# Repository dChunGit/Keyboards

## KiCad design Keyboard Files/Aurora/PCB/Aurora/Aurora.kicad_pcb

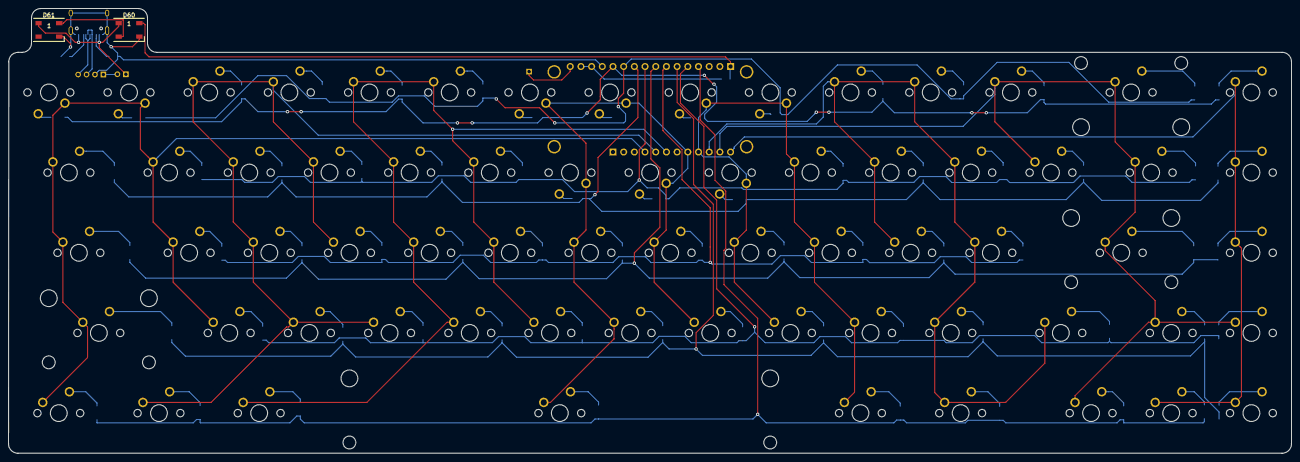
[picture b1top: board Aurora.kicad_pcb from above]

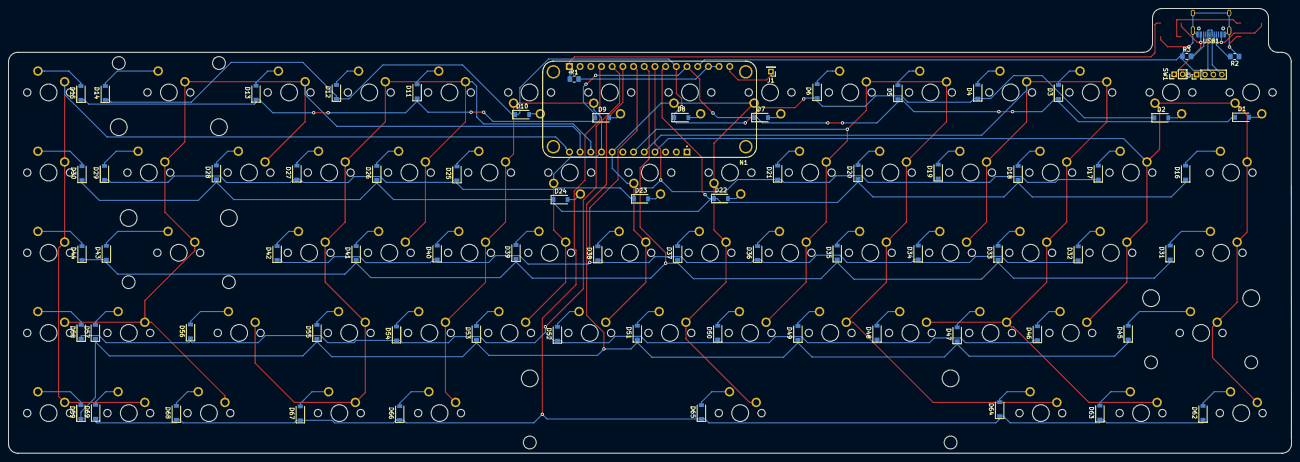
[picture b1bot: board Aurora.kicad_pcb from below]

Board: 2 copper layers, 304.9 x 105.7 mm, 144 parts (75 on the bottom side), 95 nets.

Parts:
D1, D2, D3, D4, D5, D6, D7, D8, D9, D10, D11, D12, D13, D14, D15, D16, D17, D18, D19, D20, D21, D22, D23, D24, D25, D26, D27, D28, D29, D30, D31, D32, D33, D34, D35, D36, D37, D38, D39, D40, D41, D42, D43, D44, D45, D46, D47, D48, D49, D50, D51, D52, D53, D54, D55, D56, D57, D58, D59, D62, D63, D64, D65, D66, D67, D68, D69: D_Small; D_SOD-123
D60, D61: WS2812B; LED_WS2812B_PLCC4_5.0x5.0mm_P3.2mm
J1: Conn_01x01; PinHeader_1x01_P2.00mm_Vertical
J2: Conn_01x04; PinHeader_1x04_P2.00mm_Vertical
MX1, MX2, MX3, MX4, MX5, MX6, MX7, MX8, MX9, MX10, MX11, MX12, MX13, MX15, MX17, MX18, MX19, MX20, MX21, MX22, MX23, MX24, MX25, MX26, MX27, MX28, MX30, MX32, MX33, MX34, MX35, MX36, MX37, MX38, MX39, MX40, MX41, MX42, MX44, MX46, MX47, MX48, MX49, MX50, MX51, MX52, MX53, MX54, MX55, MX57, MX58, MX59, MX66, MX67: MX-NoLED; MXOnly-1U-NoLED
MX14: MX-NoLED; MXOnly-2U-NoLED
MX16, MX29: MX-NoLED; MXOnly-1.5U-NoLED
MX31, MX56: MX-NoLED; MXOnly-1.75U-NoLED
MX43, MX45: MX-NoLED; MXOnly-2.25U-ReversedStabilizers-NoLED
MX60, MX61, MX62, MX64, MX65: MX-NoLED; MXOnly-1.25U-NoLED
MX63: MX-NoLED; MXOnly-6.25U-ReversedStabilizers-NoLED
N1: nrf52; adafruit_feather
R1, R2, R3: R_Small; R_0805_2012Metric_Pad1.15x1.40mm_HandSolder
SW1: SW_SPST; PinHeader_1x02_P2.00mm_Vertical
USB1: HRO-TYPE-C-31-M-12

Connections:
+3V3: N1.2, N1.3, R1.2
+5V: D60.1, D61.1, SW1.1, USB1.2, USB1.11
Col0: MX1.1, MX2.1, MX16.1, MX17.1, MX31.1, MX32.1, MX45.1, MX46.1, MX60.1, N1.20
Col1: MX3.1, MX4.1, MX18.1, MX19.1, MX33.1, MX34.1, MX47.1, MX48.1, MX61.1, N1.21
Col2: MX5.1, MX6.1, MX20.1, MX21.1, MX35.1, MX36.1, MX49.1, MX50.1, MX62.1, N1.22
Col3: MX7.1, MX8.1, MX22.1, MX23.1, MX37.1, MX38.1, MX51.1, MX52.1, MX63.1, N1.24
Col4: MX9.1, MX10.1, MX24.1, MX25.1, MX39.1, MX40.1, MX53.1, MX54.1, MX64.1, N1.25
Col5: MX11.1, MX12.1, MX26.1, MX27.1, MX41.1, MX42.1, MX55.1, MX56.1, MX65.1, N1.26
Col6: MX13.1, MX14.1, MX28.1, MX29.1, MX43.1, MX57.1, MX58.1, MX66.1, N1.27
Col7: MX15.1, MX30.1, MX44.1, MX59.1, MX67.1, N1.28
D+: J2.3, USB1.6, USB1.8
D-: J2.4, USB1.5, USB1.7
GND: D60.3, D61.3, J2.2, N1.4, R2.1, R3.1, USB1.1, USB1.12, USB1.13
LED: D60.4, N1.16, R1.1
unnamed: D1.2, MX1.2
unnamed: D2.2, MX2.2
unnamed: D3.2, MX3.2
unnamed: D4.2, MX4.2
unnamed: D5.2, MX5.2
unnamed: D6.2, MX6.2
unnamed: D7.2, MX7.2
unnamed: D8.2, MX8.2
unnamed: D9.2, MX9.2
unnamed: D10.2, MX10.2
unnamed: D11.2, MX11.2
unnamed: D12.2, MX12.2
unnamed: D13.2, MX13.2
unnamed: D14.2, MX14.2
unnamed: D15.2, MX15.2
unnamed: D16.2, MX16.2
unnamed: D17.2, MX17.2
unnamed: D18.2, MX18.2
unnamed: D19.2, MX19.2
unnamed: D20.2, MX20.2
unnamed: D21.2, MX21.2
unnamed: D22.2, MX22.2
unnamed: D23.2, MX23.2
unnamed: D24.2, MX24.2
unnamed: D25.2, MX25.2
unnamed: D26.2, MX26.2
unnamed: D27.2, MX27.2
unnamed: D28.2, MX28.2
unnamed: D29.2, MX29.2
unnamed: D30.2, MX30.2
unnamed: D31.2, MX31.2
unnamed: D32.2, MX32.2
unnamed: D33.2, MX33.2
unnamed: D34.2, MX34.2
unnamed: D35.2, MX35.2
unnamed: D36.2, MX36.2
unnamed: D37.2, MX37.2
unnamed: D38.2, MX38.2
unnamed: D39.2, MX39.2
unnamed: D40.2, MX40.2
unnamed: D41.2, MX41.2
unnamed: D42.2, MX42.2
unnamed: D43.2, MX43.2
unnamed: D44.2, MX44.2
unnamed: D45.2, MX45.2
unnamed: D46.2, MX46.2
unnamed: D47.2, MX47.2
unnamed: D48.2, MX48.2
unnamed: D49.2, MX49.2
unnamed: D50.2, MX50.2
unnamed: D51.2, MX51.2
unnamed: D52.2, MX52.2
unnamed: D53.2, MX53.2
unnamed: D54.2, MX54.2
unnamed: D55.2, MX55.2
unnamed: D56.2, MX56.2
unnamed: D57.2, MX57.2
unnamed: D58.2, MX58.2
unnamed: D59.2, MX59.2
unnamed: D60.2, D61.4
unnamed: D62.2, MX60.2
unnamed: D63.2, MX61.2
unnamed: D64.2, MX62.2
unnamed: D65.2, MX63.2
unnamed: D66.2, MX64.2
unnamed: D67.2, MX65.2
unnamed: D68.2, MX66.2
unnamed: D69.2, MX67.2
unnamed: J1.1, N1.1
unnamed: J2.1, SW1.2
unnamed: R2.2, USB1.4
unnamed: R3.2, USB1.10
Row0: D1.1, D3.1, D5.1, D7.1, D9.1, D11.1, D13.1, D15.1, N1.5
Row1: D2.1, D4.1, D6.1, D8.1, D10.1, D12.1, D14.1, N1.6
Row2: D16.1, D18.1, D20.1, D22.1, D24.1, D26.1, D28.1, D30.1, N1.7
Row3: D17.1, D19.1, D21.1, D23.1, D25.1, D27.1, D29.1, N1.8
Row4: D31.1, D33.1, D35.1, D37.1, D39.1, D41.1, D43.1, D44.1, N1.9
Row5: D32.1, D34.1, D36.1, D38.1, D40.1, D42.1, N1.10
Row6: D45.1, D47.1, D49.1, D51.1, D53.1, D55.1, D57.1, D59.1, N1.11
Row7: D46.1, D48.1, D50.1, D52.1, D54.1, D56.1, D58.1, N1.12
Row8: D62.1, D63.1, D64.1, D65.1, D66.1, D67.1, D68.1, D69.1, N1.13

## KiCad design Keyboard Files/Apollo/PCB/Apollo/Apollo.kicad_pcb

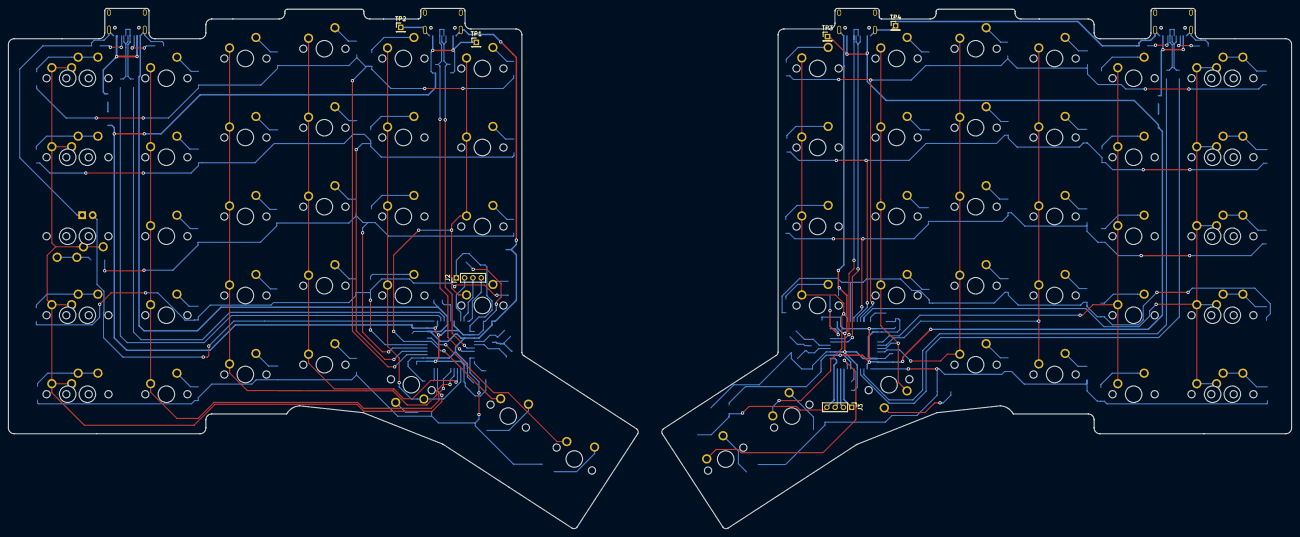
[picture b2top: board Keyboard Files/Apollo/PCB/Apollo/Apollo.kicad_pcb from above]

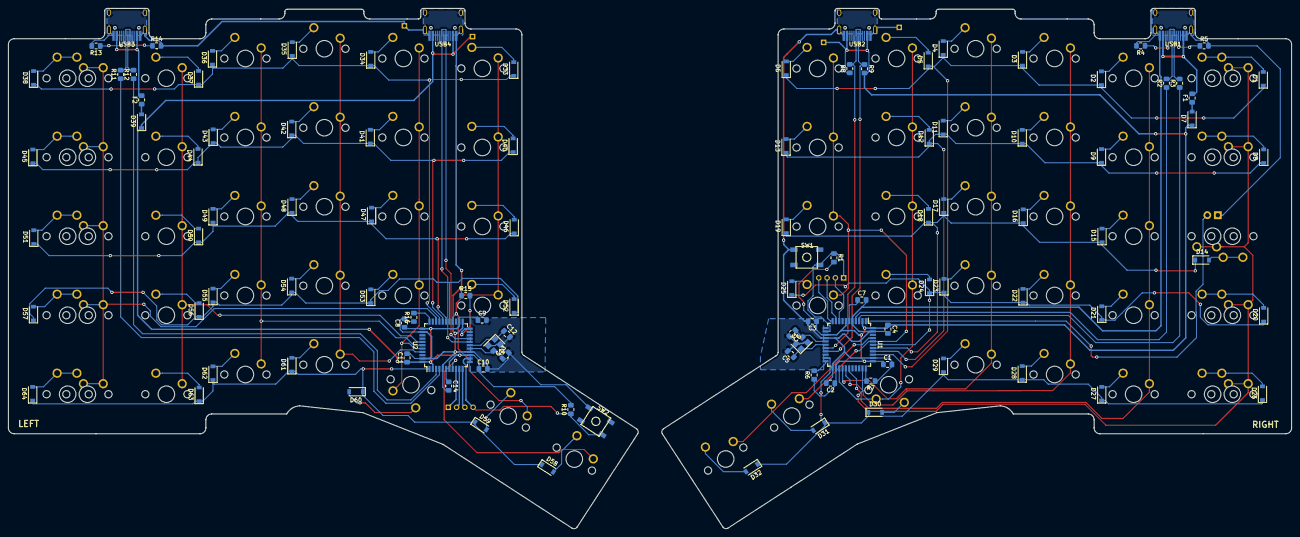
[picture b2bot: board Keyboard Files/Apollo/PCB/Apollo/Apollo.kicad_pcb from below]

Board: 2 copper layers, 309.4 x 125.5 mm, 184 parts (106 on the bottom side), 129 nets.

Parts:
C1, C2, C3, C8, C9, C10: 0.1uF; C_0805_2012Metric_Pad1.15x1.40mm_HandSolder
C4, C11: 10uF; C_0805_2012Metric_Pad1.15x1.40mm_HandSolder
C5, C6, C12, C13: 22pF; C_0805_2012Metric_Pad1.15x1.40mm_HandSolder
C7, C14: 1uF; C_0805_2012Metric_Pad1.15x1.40mm_HandSolder
D1, D2, D3, D4, D5, D6, D8, D9, D10, D11, D12, D13, D14, D15, D16, D17, D18, D19, D20, D21, D22, D23, D24, D25, D26, D27, D28, D29, D30, D31, D32, D33, D34, D35, D36, D37, D38, D40, D41, D42, D43, D44, D45, D46, D47, D48, D49, D50, D51, D52, D53, D54, D55, D56, D57, D58, D59, D60, D61, D62, D63, D64: D_Small; D_SOD-123
D7, D39: Schottky; D_SOD-123
F1, F2: Polyfuse_Small; Fuse_0805_2012Metric_Pad1.15x1.40mm_HandSolder
J2, J3: Conn_01x04; PinHeader_1x04_P2.00mm_Vertical
MX1, MX7, MX13, MX19, MX25, MX37, MX43, MX49, MX55, MX62: MX-NoLED; MXOnly-1.5U-NoLED
MX2, MX3, MX4, MX5, MX6, MX8, MX9, MX10, MX11, MX12, MX14, MX15, MX16, MX17, MX18, MX20, MX21, MX22, MX23, MX24, MX26, MX27, MX28, MX29, MX32, MX33, MX34, MX35, MX36, MX38, MX39, MX40, MX41, MX42, MX44, MX45, MX46, MX47, MX48, MX50, MX51, MX52, MX53, MX54, MX58, MX59, MX60, MX61, MX63, MX64, MX66, MX67, MX68, MX69, MX70, MX71, MX72: MX-NoLED; MXOnly-1U-NoLED
MX30, MX31, MX56, MX57: MX-NoLED; MXOnly-1.5U-Vertical-NoLED
MX65: MX-LED; MXOnly-1U
R1, R6, R7, R10, R15, R16: 10k; R_0805_2012Metric_Pad1.15x1.40mm_HandSolder
R2, R3, R11, R12: 22; R_0805_2012Metric_Pad1.15x1.40mm_HandSolder
R4, R5, R13, R14: 5.1k; R_0805_2012Metric_Pad1.15x1.40mm_HandSolder
R8, R9: 4.7k; R_0805_2012Metric_Pad1.15x1.40mm_HandSolder
SW1, SW2: SW_Push; SKQGADE010
TP1, TP2, TP3, TP4: TestPoint; PinHeader_1x01_P2.00mm_Vertical
U1, U2: ATmega32U4-MU; TQFP-44_10x10mm_P0.8mm
USB1, USB2, USB3, USB4: HRO-TYPE-C-31-M-12; HRO-TYPE-C-31-M-12-HandSoldering
Y1, Y2: Crystal_GND24_Small; Crystal_SMD_3225-4Pin_3.2x2.5mm

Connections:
+5V: C1.1, C2.1, C3.1, C4.1, D7.1, R1.2, R6.1, R8.1, R9.2, TP1.1, U1.2, U1.7, U1.14, U1.24, U1.34, U1.44, USB2.2, USB2.11
+5VA: C8.1, C9.1, C10.1, C11.1, D39.1, R10.2, TP3.1, U2.2, U2.7, U2.14, U2.24, U2.34, U2.44, USB4.2, USB4.11
CapsLED: MX65.3, U1.1
Col0: MX1.1, MX7.1, MX13.1, MX19.1, MX25.1, MX63.1, MX64.1, MX65.1, MX66.1, MX67.1, U1.32
Col0_1: MX56.1, U2.8
Col1: MX2.1, MX8.1, MX14.1, MX20.1, MX26.1, U1.28
Col1_1: MX32.1, MX38.1, MX44.1, MX50.1, MX57.1, U2.26
Col2: MX3.1, MX9.1, MX15.1, MX21.1, MX27.1, U1.27
Col2_1: MX33.1, MX39.1, MX45.1, MX51.1, MX58.1, U2.40
Col3: MX4.1, MX10.1, MX16.1, MX22.1, MX28.1, U1.26
Col3_1: MX34.1, MX40.1, MX46.1, MX52.1, MX59.1, U2.41
Col4: MX5.1, MX11.1, MX17.1, MX23.1, MX29.1, U1.25
Col4_1: MX35.1, MX41.1, MX47.1, MX53.1, MX60.1, U2.39
Col5: MX6.1, MX12.1, MX18.1, MX24.1, MX30.1, U1.40
Col5_1: MX36.1, MX42.1, MX48.1, MX54.1, MX61.1, U2.38
Col6: MX31.1, U1.41
Col6_1: MX37.1, MX43.1, MX49.1, MX55.1, MX62.1, MX68.1, MX69.1, MX70.1, MX71.1, MX72.1, U2.31
D1_+: R11.1, U2.4
D1_-: R12.1, U2.3
D+: R2.1, U1.4
D-: R3.1, U1.3
GND: C1.2, C2.2, C3.2, C4.2, C5.2, C6.2, C7.2, MX65.4, R4.2, R5.2, R7.1, SW1.1, TP2.1, U1.5, U1.15, U1.23, U1.35, U1.43, USB1.1, USB1.12, USB1.13, USB2.1, USB2.12, USB2.13, Y1.2, Y1.4
GNDA: C8.2, C9.2, C10.2, C11.2, C12.2, C13.2, C14.2, R13.2, R14.2, R15.1, R16.1, SW2.1, TP4.1, U2.5, U2.15, U2.23, U2.35, U2.43, USB3.1, USB3.12, USB3.13, USB4.1, USB4.12, USB4.13, Y2.2, Y2.4
MISO: J2.4, U1.11
MISO_1: J3.3, U2.11
MOSI: J2.3, U1.10
MOSI_1: J3.2, U2.10
unnamed: C5.1, U1.17, Y1.1
unnamed: C6.1, U1.16, Y1.3
unnamed: C7.1, U1.6
unnamed: C12.1, U2.17, Y2.1
unnamed: C13.1, U2.16, Y2.3
unnamed: C14.1, U2.6
unnamed: D1.2, MX1.2, MX63.2
unnamed: D2.2, MX2.2
unnamed: D3.2, MX3.2
unnamed: D4.2, MX4.2
unnamed: D5.2, MX5.2
unnamed: D6.2, MX6.2
unnamed: D7.2, F1.1
unnamed: D8.2, MX7.2, MX64.2
unnamed: D9.2, MX8.2
unnamed: D10.2, MX9.2
unnamed: D11.2, MX10.2
unnamed: D12.2, MX11.2
unnamed: D13.2, MX12.2
unnamed: D14.2, MX13.2, MX65.2
unnamed: D15.2, MX14.2
unnamed: D16.2, MX15.2
unnamed: D17.2, MX16.2
unnamed: D18.2, MX17.2
unnamed: D19.2, MX18.2
unnamed: D20.2, MX19.2, MX66.2
unnamed: D21.2, MX20.2
unnamed: D22.2, MX21.2
unnamed: D23.2, MX22.2
unnamed: D24.2, MX23.2
unnamed: D25.2, MX24.2
unnamed: D26.2, MX25.2, MX67.2
unnamed: D27.2, MX26.2
unnamed: D28.2, MX27.2
unnamed: D29.2, MX28.2
unnamed: D30.2, MX29.2
unnamed: D31.2, MX30.2
unnamed: D32.2, MX31.2
unnamed: D33.2, MX32.2
unnamed: D34.2, MX33.2
unnamed: D35.2, MX34.2
unnamed: D36.2, MX35.2
unnamed: D37.2, MX36.2
unnamed: D38.2, MX37.2, MX68.2
unnamed: D39.2, F2.1
unnamed: D40.2, MX38.2
unnamed: D41.2, MX39.2
unnamed: D42.2, MX40.2
unnamed: D43.2, MX41.2
unnamed: D44.2, MX42.2
unnamed: D45.2, MX43.2, MX69.2
unnamed: D46.2, MX44.2
unnamed: D47.2, MX45.2
unnamed: D48.2, MX46.2
unnamed: D49.2, MX47.2
unnamed: D50.2, MX48.2
unnamed: D51.2, MX49.2, MX70.2
unnamed: D52.2, MX50.2
unnamed: D53.2, MX51.2
unnamed: D54.2, MX52.2
unnamed: D55.2, MX53.2
unnamed: D56.2, MX54.2
unnamed: D57.2, MX55.2, MX71.2
unnamed: D58.2, MX56.2
unnamed: D59.2, MX57.2
unnamed: D60.2, MX58.2
unnamed: D61.2, MX59.2
unnamed: D62.2, MX60.2
unnamed: D63.2, MX61.2
unnamed: D64.2, MX62.2, MX72.2
unnamed: F1.2, USB1.2, USB1.11
unnamed: F2.2, USB3.2, USB3.11
unnamed: R2.2, USB1.6, USB1.8
unnamed: R3.2, USB1.5, USB1.7
unnamed: R4.1, USB1.10
unnamed: R5.1, USB1.4
unnamed: R6.2, U1.22
unnamed: R7.2, U1.33
unnamed: R11.2, USB3.6, USB3.8
unnamed: R12.2, USB3.5, USB3.7
unnamed: R13.1, USB3.10
unnamed: R14.1, USB3.4
unnamed: R15.2, U2.22
unnamed: R16.2, U2.33
RST: J2.1, R1.1, SW1.2, U1.13
RST_1: J3.4, R10.1, SW2.2, U2.13
Row0: D1.1, D2.1, D3.1, D4.1, D5.1, D6.1, U1.36
Row0_1: D33.1, D34.1, D35.1, D36.1, D37.1, D38.1, U2.30
Row1: D8.1, D9.1, D10.1, D11.1, D12.1, D13.1, U1.37
Row1_1: D40.1, D41.1, D42.1, D43.1, D44.1, D45.1, U2.29
Row2: D14.1, D15.1, D16.1, D17.1, D18.1, D19.1, U1.38
Row2_1: D46.1, D47.1, D48.1, D49.1, D50.1, D51.1, U2.28
Row3: D20.1, D21.1, D22.1, D23.1, D24.1, D25.1, U1.39
Row3_1: D52.1, D53.1, D54.1, D55.1, D56.1, D57.1, U2.27
Row4: D26.1, D27.1, D28.1, D29.1, D30.1, D31.1, D32.1, U1.21
Row4_1: D58.1, D59.1, D60.1, D61.1, D62.1, D63.1, D64.1, U2.1
SCK: J2.2, U1.9
SCK_1: J3.1, U2.9
SCL: R8.2, U1.18, USB2.6, USB2.8
SCL_1: U2.18, USB4.6, USB4.8
SDA: R9.1, U1.19, USB2.5, USB2.7
SDA_1: U2.19, USB4.5, USB4.7

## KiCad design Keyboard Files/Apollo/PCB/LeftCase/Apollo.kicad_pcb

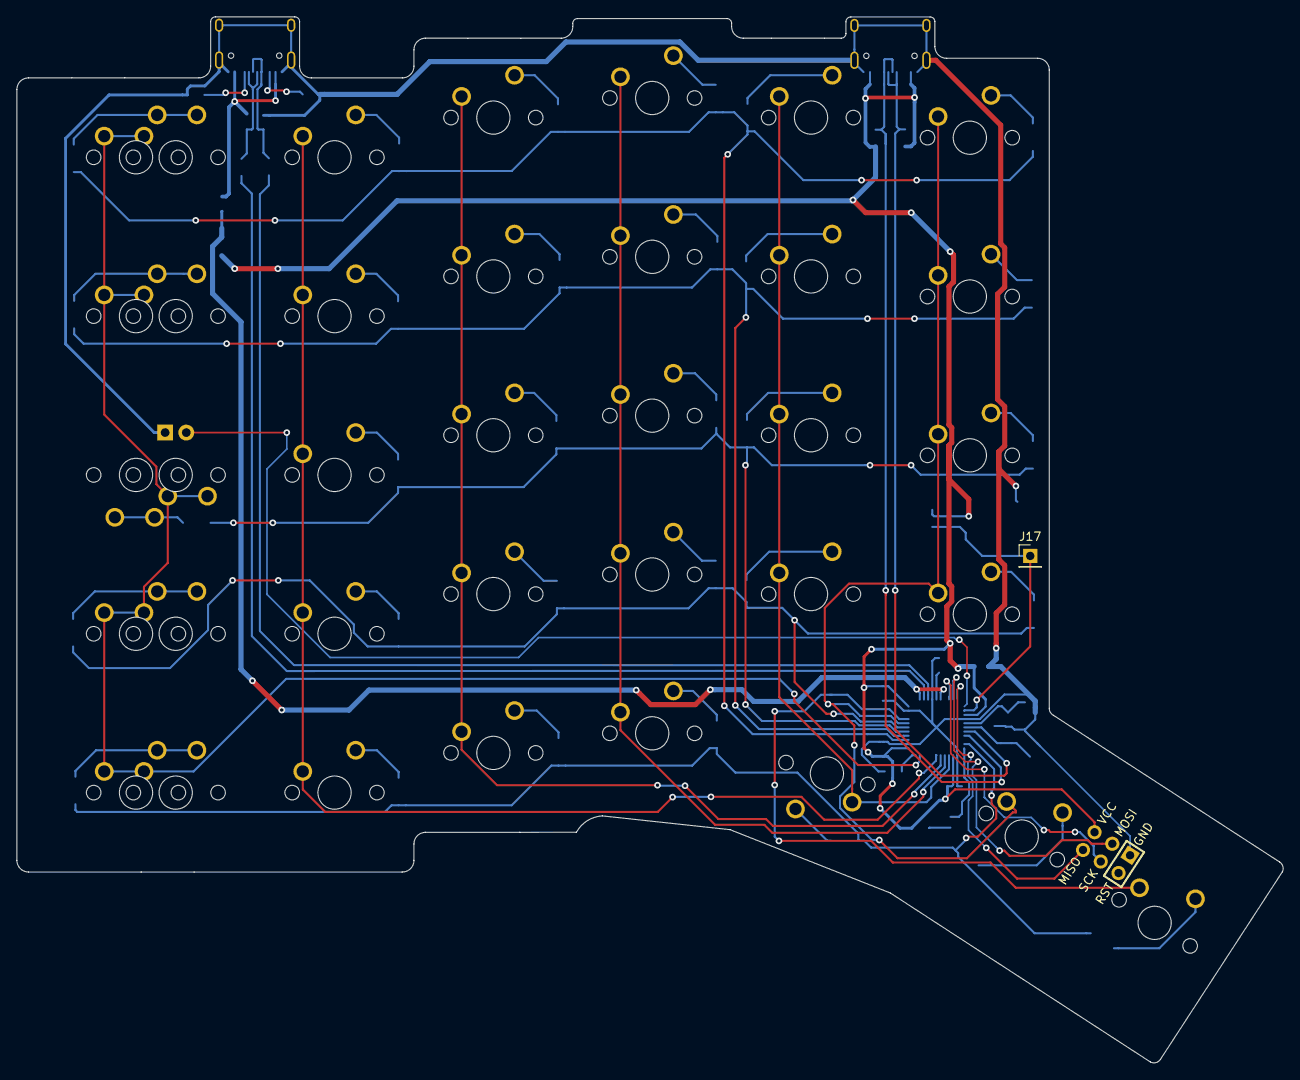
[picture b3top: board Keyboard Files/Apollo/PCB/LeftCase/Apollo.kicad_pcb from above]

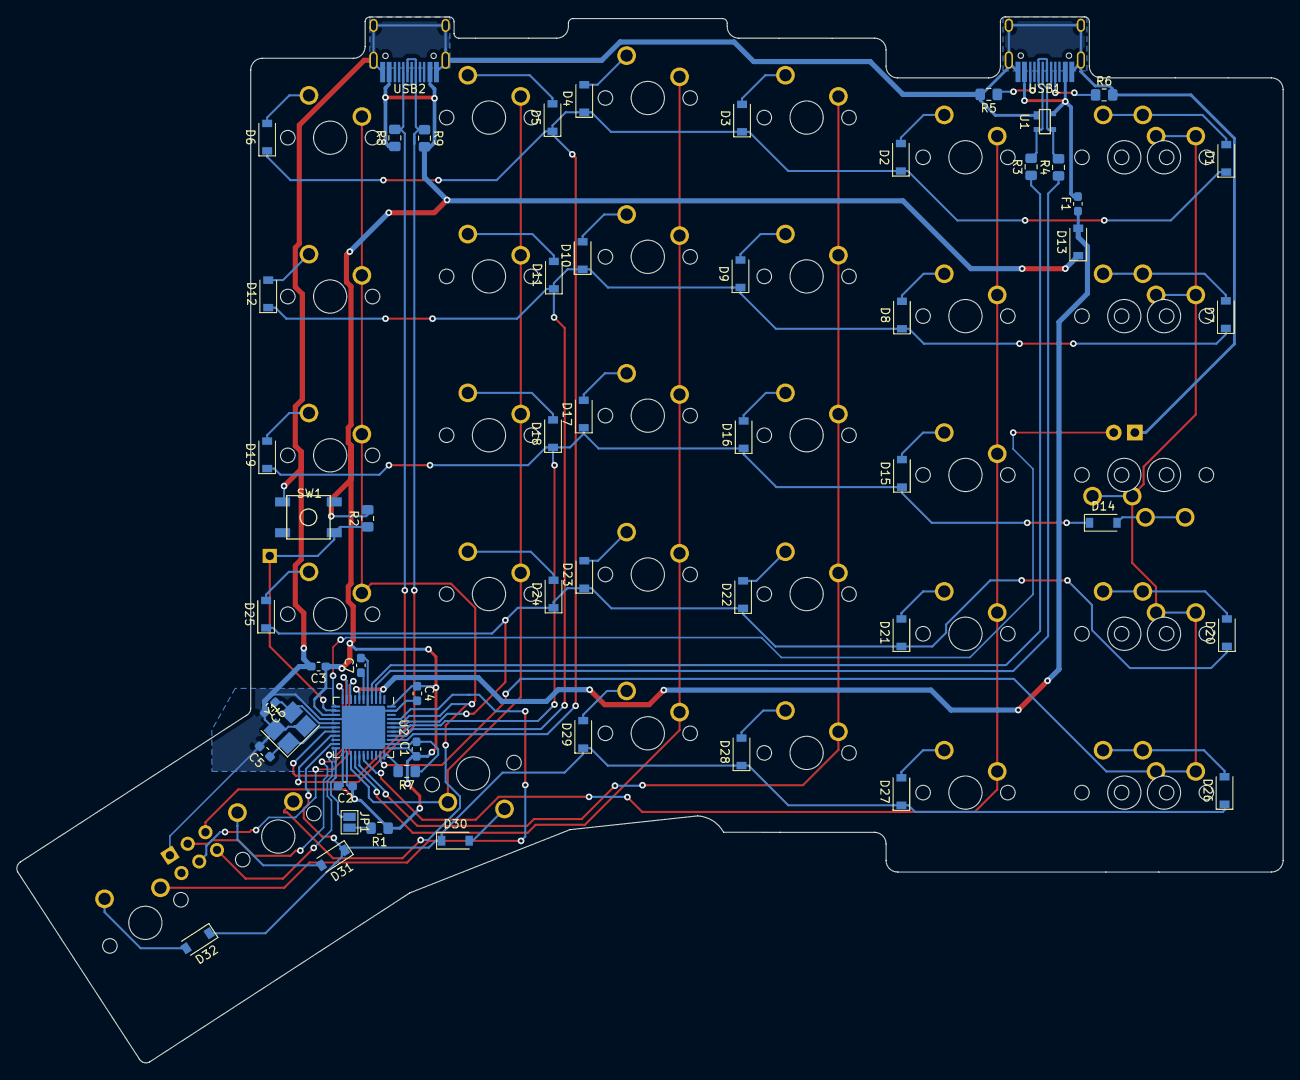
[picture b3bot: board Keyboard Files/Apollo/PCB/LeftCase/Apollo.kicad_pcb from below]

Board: 2 copper layers, 151.9 x 125.5 mm, 94 parts (56 on the bottom side), 66 nets.

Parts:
C1, C2, C3: 0.1uF; C_0603_1608Metric_Pad1.05x0.95mm_HandSolder
C4: 10uF; C_0603_1608Metric_Pad1.05x0.95mm_HandSolder
C5, C6: 22pF; C_0603_1608Metric_Pad1.05x0.95mm_HandSolder
C7: 1uF; C_0603_1608Metric_Pad1.05x0.95mm_HandSolder
D1, D2, D3, D4, D5, D6, D7, D8, D9, D10, D11, D12, D14, D15, D16, D17, D18, D19, D20, D21, D22, D23, D24, D25, D26, D27, D28, D29, D30, D31, D32: D_Small; D_SOD-123
D13: Schottky; D_SOD-123
F1: 500mA; Fuse_0603_1608Metric_Pad1.05x0.95mm_HandSolder
J1: AVR-ISP-6; Reset_Pretty-Mask
J17: Conn_01x01; PinHeader_1x01_P2.54mm_Vertical
JP1: Jumper_NO; SolderJumper-2_P1.3mm_Open_Pad1.0x1.5mm
MX1, MX7, MX13, MX19, MX25: MX-NoLED; MXOnly-1.5U-NoLED
MX2, MX3, MX4, MX5, MX6, MX8, MX9, MX10, MX11, MX12, MX14, MX15, MX16, MX17, MX18, MX20, MX21, MX22, MX23, MX24, MX26, MX27, MX28, MX29, MX63, MX64, MX66, MX67: MX-NoLED; MXOnly-1U-NoLED
MX30, MX31: MX-NoLED; MXOnly-1.5U-Vertical-NoLED
MX65: MX-LED; MXOnly-1U
R1, R2, R7: 10k; R_0805_2012Metric_Pad1.15x1.40mm_HandSolder
R3, R4: 22; R_0805_2012Metric_Pad1.15x1.40mm_HandSolder
R5, R6: 5.1k; R_0805_2012Metric_Pad1.15x1.40mm_HandSolder
R8, R9: 4.7k; R_0805_2012Metric_Pad1.15x1.40mm_HandSolder
SW1: SW_Push; SKQGADE010
U1: PRTR5V0U2X; SOT143B
U2: ATmega32U4-MU; QFN-44-1EP_7x7mm_P0.5mm_EP5.2x5.2mm
USB1, USB2: HRO-TYPE-C-31-M-12; HRO-TYPE-C-31-M-12-HandSoldering
Y1: Crystal_GND24_Small; Crystal_SMD_3225-4Pin_3.2x2.5mm_HandSoldering

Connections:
+5V: C1.1, C2.1, C3.1, C4.1, D13.1, J1.2, R1.1, R2.2, R8.1, R9.2, U2.14, U2.24, U2.34, U2.44, USB2.2, USB2.11
CapsLED: MX65.3, U2.12
Col0: MX1.1, MX7.1, MX13.1, MX19.1, MX25.1, MX63.1, MX64.1, MX65.1, MX66.1, MX67.1, U2.32
Col1: MX2.1, MX8.1, MX14.1, MX20.1, MX26.1, U2.28
Col2: MX3.1, MX9.1, MX15.1, MX21.1, MX27.1, U2.27
Col3: MX4.1, MX10.1, MX16.1, MX22.1, MX28.1, U2.26
Col4: MX5.1, MX11.1, MX17.1, MX23.1, MX29.1, U2.25
Col5: MX6.1, MX12.1, MX18.1, MX24.1, MX30.1, U2.40
Col6: MX31.1, U2.41
D+: R3.1, U2.4
D-: R4.1, U2.3
GND: C1.2, C2.2, C3.2, C4.2, C5.2, C6.2, C7.2, J1.6, MX65.4, R5.2, R6.2, R7.1, SW1.1, U1.1, U2.5, U2.15, U2.23, U2.35, U2.43, U2.45, USB1.1, USB1.12, USB1.13, USB2.1, USB2.12, USB2.13, Y1.2, Y1.4
HDETECT: JP1.1, U2.22
MISO: J1.1, U2.11
MOSI: J1.4, U2.10
unnamed: C5.1, U2.17, Y1.1
unnamed: C6.1, U2.16, Y1.3
unnamed: C7.1, U2.6
unnamed: D1.2, MX1.2, MX63.2
unnamed: D2.2, MX2.2
unnamed: D3.2, MX3.2
unnamed: D4.2, MX4.2
unnamed: D5.2, MX5.2
unnamed: D6.2, MX6.2
unnamed: D7.2, MX7.2, MX64.2
unnamed: D8.2, MX8.2
unnamed: D9.2, MX9.2
unnamed: D10.2, MX10.2
unnamed: D11.2, MX11.2
unnamed: D12.2, MX12.2
unnamed: D14.2, MX13.2, MX65.2
unnamed: D15.2, MX14.2
unnamed: D16.2, MX15.2
unnamed: D17.2, MX16.2
unnamed: D18.2, MX17.2
unnamed: D19.2, MX18.2
unnamed: D20.2, MX19.2, MX66.2
unnamed: D21.2, MX20.2
unnamed: D22.2, MX21.2
unnamed: D23.2, MX22.2
unnamed: D24.2, MX23.2
unnamed: D25.2, MX24.2
unnamed: D26.2, MX25.2, MX67.2
unnamed: D27.2, MX26.2
unnamed: D28.2, MX27.2
unnamed: D29.2, MX28.2
unnamed: D30.2, MX29.2
unnamed: D31.2, MX30.2
unnamed: D32.2, MX31.2
unnamed: JP1.2, R1.2
unnamed: R3.2, U1.2, USB1.6, USB1.8
unnamed: R4.2, U1.3, USB1.5, USB1.7
unnamed: R5.1, USB1.10
unnamed: R6.1, USB1.4
unnamed: R7.2, U2.33
RST: J17.1, R2.1, SW1.2, U2.13
Row0: D1.1, D2.1, D3.1, D4.1, D5.1, D6.1, U2.36
Row1: D7.1, D8.1, D9.1, D10.1, D11.1, D12.1, U2.37
Row2: D14.1, D15.1, D16.1, D17.1, D18.1, D19.1, U2.38
Row3: D20.1, D21.1, D22.1, D23.1, D24.1, D25.1, U2.39
Row4: D26.1, D27.1, D28.1, D29.1, D30.1, D31.1, D32.1, U2.21
SCK: J1.3, U2.9
SCL: R8.2, U2.18, USB2.6, USB2.8
SDA: R9.1, U2.19, USB2.5, USB2.7
VBUS: D13.2, F1.1, U2.2, U2.7
VCC: F1.2, U1.4, USB1.2, USB1.11

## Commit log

2019-02-16 Add zero64 files
2019-09-27 Add decals
2019-09-27 Update files
2019-09-27 Add dactyl manuform mini
2020-02-17 Add Apollo PCB
2020-02-17 Reorganize folder structure
2020-02-23 Update Apollo
2020-02-24 Add Apollo plates
2020-02-24 Update Apollo plates, export pcb and plate svgs
2020-02-26 Increase Apollo plate bezel
2020-02-28 redo plate files
2020-02-28 Redo thumb keys plates
2020-03-02 Add renders and modify plate files
2020-03-03 Add apollo gerbers
2020-03-30 Add Aurora Keyboard
